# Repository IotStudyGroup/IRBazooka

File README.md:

# IRBazooka

This is the initial repository for our IoT Study Group.

The aim of this project is to create an automated way of turning off all the AC units in the office at some specified time, with the intention of reducing our energy consumption. Alexa integration is also on the roadmap, in order to control the AC units with only our voice power.

# Instructions

```bash
$ git clone --recursive https://github.com/IotStudyGroup/IRBazooka.git
```

## Folder structure

- Eagle
  - PCB files.
- Led-holder
  - 3D Printed files for the LED holder. You don't actually need it. But it makes it easier to position the LEDs.
- NodeMCU
  - Firmware (WORKING IN PROGRESS - NOT USABLE YET)
- OpenMQTTGateway (git submodule)
  - open firmware that works great!

# Bill Of Materials
These are the components necessary to build the board
```
Qty   Value            Description

 2    10kΩ             10kΩ resistor
 3    1kΩ              1kΩ resistor
 7    2N3904           NPN Transistror
 1    S8550            PNP Transistror
 1    ESP12E_DEVKIT    NodeMCU v2
 6    LED-IRTSAL6100   Infrared LED (IR)
 1    TSOP4838         IR Receiver and Demodulator
 ```
 Link for buying at Filipe Flop:<br>
 * [10kΩ resistor](https://www.filipeflop.com/produto/resistor-10k%CF%89-14w-x20-unidades/)<br>
 * [1kΩ resistor](https://www.filipeflop.com/produto/resistor-1k%CF%89-14w-x20-unidades/)<br>
 * [2N3904](https://www.filipeflop.com/produto/transistor-2n3904-npn-x10-unidades/)<br>
 * [S8550](https://www.filipeflop.com/produto/transistor-s8550-pnp-x10-unidades/)<br>
 * [ESP12E_DEVKIT](https://www.filipeflop.com/produto/modulo-wifi-esp8266-nodemcu-esp-12/)<br>
 * [LED-IRTSAL6100](https://www.filipeflop.com/produto/led-emissor-infravermelho-ir-5mm/)<br>
 * [TSOP4838](https://www.filipeflop.com/produto/receptor-infravermelho-ir-tsop4838/)<br>

# Pins:
- D1 (GPIO5) - IR Receiver
- D2 (GPIO4) - IR LEDs

# How to use it:
The easiest way is to use it with [ESPHome](https://esphome.io/index.html)
Here's an example of a configuration of a LG AC:
```yaml
substitutions:
  name: "Bedroom AC"

esphome:
  name: bedroom_ac
  platform: ESP8266
  board: nodemcuv2

wifi:
  ssid: !secret wifi_ssid
  password: !secret wifi_password

  # Enable fallback hotspot (captive portal) in case wifi connection fails
  ap:
    ssid: "Bedroom Ac Fallback Hotspot"
    password: !secret wifi_password

captive_portal:

# Enable logging
logger:

# Enable Home Assistant API
api:

ota:

remote_receiver:
  id: receiver
  pin:
    number: D1
    inverted: true
  dump: raw

remote_transmitter:
  pin: D2
  carrier_duty_percent: 50%

# Using a temperature sensor from Home Assistant
sensor:
  - platform: homeassistant
    name: "temp sensor"
    internal: true
    id: temp_sensor
    entity_id: sensor.bedroom_temperature

climate:
  name: "${name}"
  platform: climate_ir_lg
  receiver_id: receiver
  sensor: temp_sensor
  header_high: 3265us # AC Units from LG in Brazil, for example use these timings
  header_low: 9856us
```

# References
- Circuit inspired by [Harald Braun's IRBridge](https://www.hackster.io/har-bra/irbridge-controlling-ir-devices-via-alexa-web-interface-66ca06)

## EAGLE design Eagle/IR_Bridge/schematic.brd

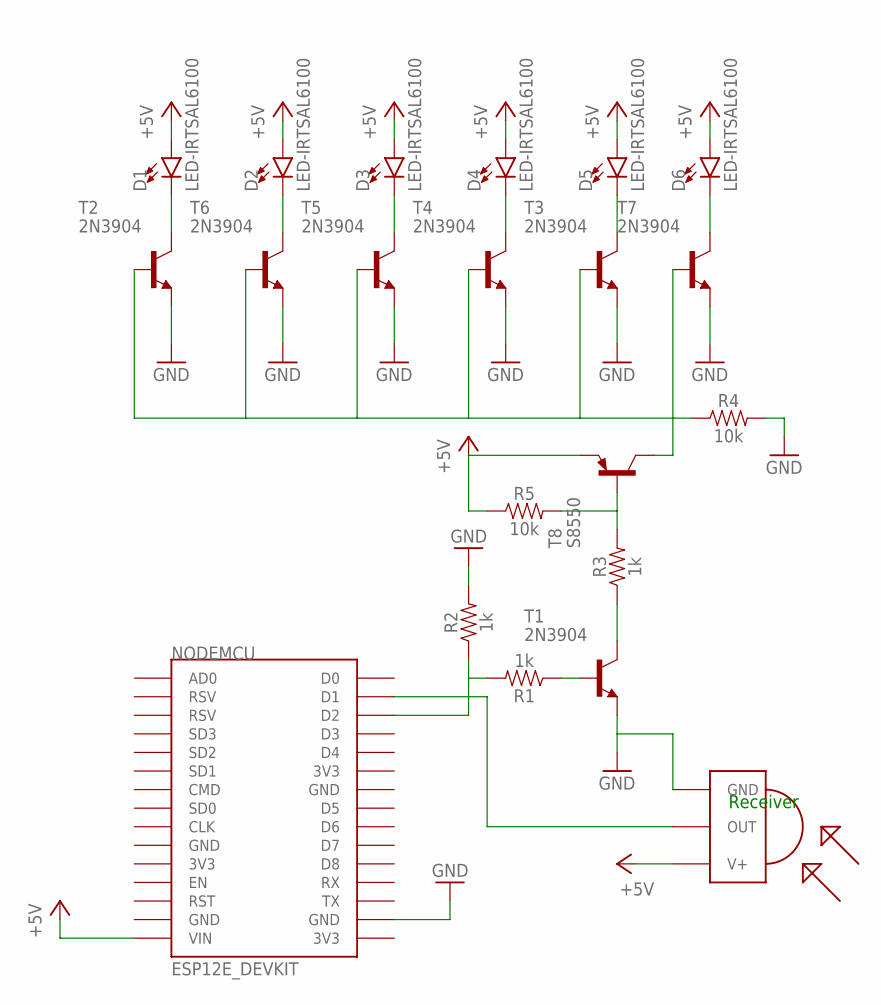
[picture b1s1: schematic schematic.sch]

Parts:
D1, D2, D3, D4, D5, D6: LED-IRTSAL6100; LED_5MM
NODEMCU: ESP12E_DEVKIT
R1, R2, R3: 1k; AXIAL-0.3; MPN MCF 0.25W 1K
R4, R5: 10k; AXIAL-0.3; MPN MCF 0.25W 10K
RECEIVER: TSOP4838; TSOP18XX; MPN TSOP4838
T1, T2, T3, T4, T5, T6, T7: 2N3904; TO92; MPN 2N3904BU
T8: S8550; TO92-EBC

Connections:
+5V: D1.A, D2.A, D3.A, D4.A, D5.A, D6.A, NODEMCU.VIN, R5.P$1 (1), RECEIVER.VCC (V+), T8.E
GND: NODEMCU.GND@3 (GND), R2.P$2 (2), R4.P$2 (2), RECEIVER.GND, T1.3 (E), T2.3 (E), T3.3 (E), T4.3 (E), T5.3 (E), T6.3 (E), T7.3 (E)
unnamed: NODEMCU.D2, R1.P$2 (2), R2.P$1 (1)
unnamed: R4.P$1 (1), T2.2 (B), T3.2 (B), T4.2 (B), T5.2 (B), T6.2 (B), T7.2 (B), T8.C
unnamed: R1.P$1 (1), T1.2 (B)
unnamed: R3.P$1 (1), T1.1 (C)
unnamed: R3.P$2 (2), R5.P$2 (2), T8.B
unnamed: NODEMCU.D1, RECEIVER.OUT
unnamed: D6.K (C), T7.1 (C)
unnamed: D1.K (C), T2.1 (C)
unnamed: D2.K (C), T6.1 (C)
unnamed: D3.K (C), T5.1 (C)
unnamed: D4.K (C), T4.1 (C)
unnamed: D5.K (C), T3.1 (C)

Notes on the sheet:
Receiver

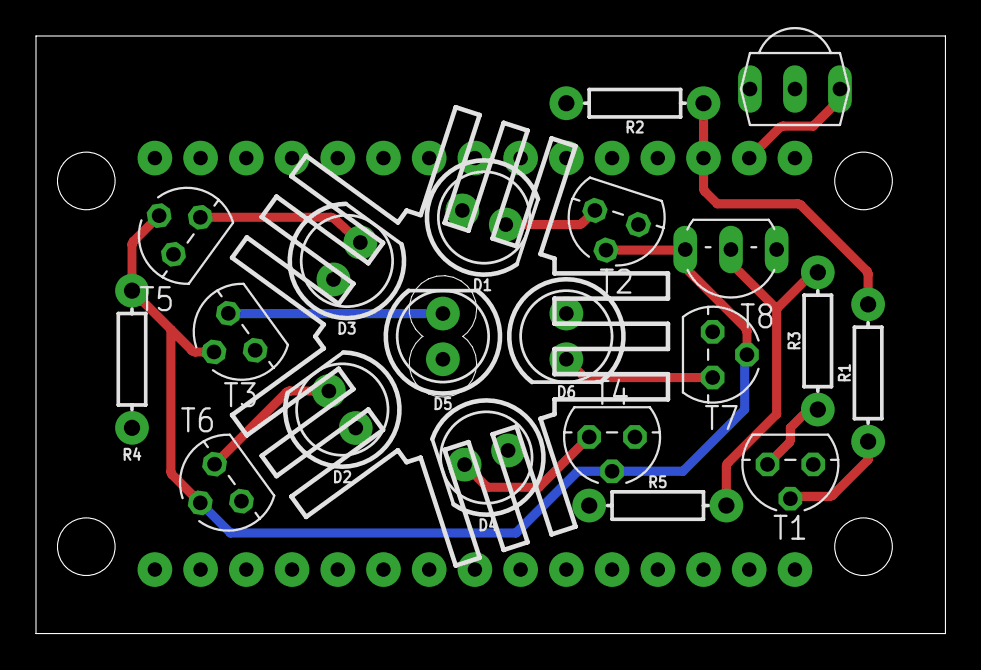
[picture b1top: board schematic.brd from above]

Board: 2 copper layers, 50.5 x 33.2 mm, 21 parts (1 on the bottom side), 14 nets.

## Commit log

2018-04-17 Updating README.md
2018-04-18 Add board files
2018-04-18 Remove files
2018-04-18 Add base files
2018-04-18 Adding .gitignore
2018-04-18 Adding send test
2018-04-18 Add led holder files
2018-04-25 Finish designing PCB
2018-04-25 Remove values from silk
2018-04-25 Implement MQTT server
2018-04-25 Fix some issues on the PCB
2018-04-25 Move some labels around
2018-04-25 Prepare board to fabricate
2018-06-14 Schematic
2018-06-14 Remove old firmware and use the projector example code as base
2018-06-18 Add board image
2018-06-21 Add bill of materials
2018-06-26 Add Links for Filipe Flop's Components page
2018-08-11 Adds OpenMQTTGateway as a git submodule
2018-10-30 Add schematic and pcb images

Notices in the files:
parts and their libraries:
SparkFun-LED: Licensing: Creative Commons ShareAlike 4.0 International - https://creativecommons.org/licenses/by-sa/4.0
